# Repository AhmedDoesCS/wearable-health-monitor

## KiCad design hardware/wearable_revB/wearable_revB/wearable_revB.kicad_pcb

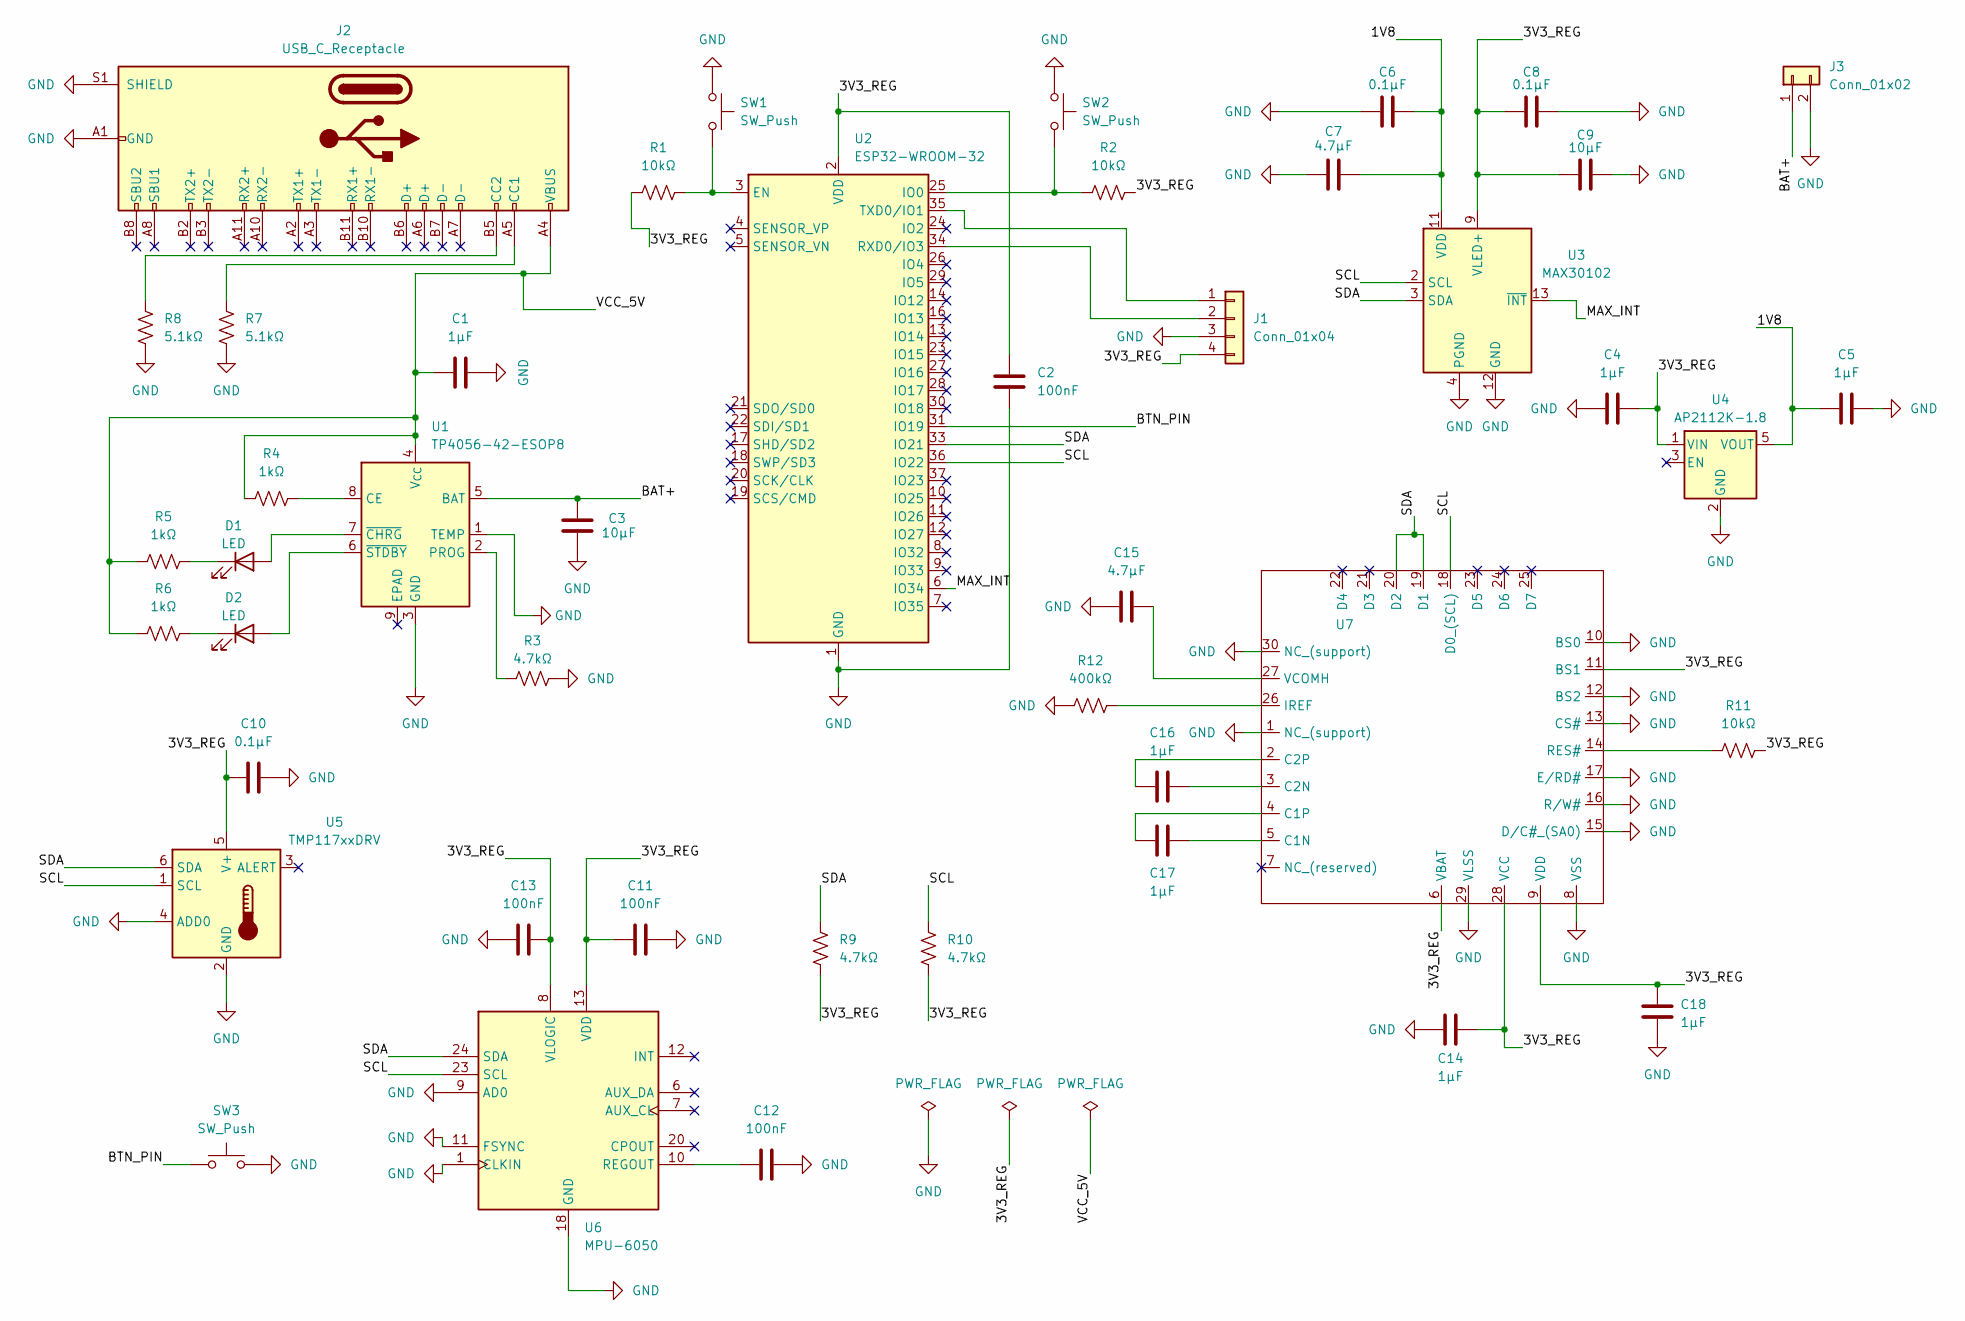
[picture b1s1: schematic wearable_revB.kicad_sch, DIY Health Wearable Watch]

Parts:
C1, C4, C5, C14, C16, C17, C18: 1µF; C_0603_1608Metric
C2, C11, C12, C13: 100nF; C_0603_1608Metric
C3, C9: 10µF; C_0603_1608Metric
C6, C8, C10: 0.1µF; C_0603_1608Metric
C7, C15: 4.7µF; C_0603_1608Metric
D1, D2: LED; LED_0603_1608Metric
J1: Conn_01x04; PinHeader_1x04_P1.27mm_Vertical_SMD_Pin1Left
J2: USB_C_Receptacle; USB_C_Receptacle_HRO_TYPE-C-31-M-12
J3: Conn_01x02; Battery_2Pin_THT
R1, R2, R11: 10kΩ; R_0603_1608Metric
R3, R9, R10: 4.7kΩ; R_0603_1608Metric
R4, R5, R6: 1kΩ; R_0603_1608Metric
R7, R8: 5.1kΩ; R_0603_1608Metric
R12: 400kΩ; R_0603_1608Metric
SW1, SW2: SW_Push; SW_SPST_B3U-1000P
SW3: SW_Push; SW_SPST_B3S-1100
U1: TP4056-42-ESOP8; SOIC-8-1EP_3.9x4.9mm_P1.27mm_EP2.41x3.3mm_ThermalVias
U2: ESP32-WROOM-32
U3: MAX30102; Maxim_OLGA-14_3.3x5.6mm_P0.8mm
U4: AP2112K-1.8; SOT-23-5
U5: TMP117xxDRV; WSON-6-1EP_2x2mm_P0.65mm_EP1x1.6mm
U6: MPU-6050; InvenSense_QFN-24_4x4mm_P0.5mm
U7: EASTRISING_ER-CON50HT-1

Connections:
/1V8: C5.1, C6.2, C7.1, U3.11 (VDD), U4.5 (VOUT)
/3V3_REG: C2.1, C4.2, C8.1, C9.1, C10.2, C11.1, C13.2, C14.2, C18.2, J1.4, R1.1, R2.2, R9.2, R10.2, R11.2, U2.2 (VDD), U3.9 (VLED+), U3.10 (VLED+), U4.1 (VIN), U5.5 (V+), U6.8 (VLOGIC), U6.13 (VDD), U7.6 (VBAT), U7.9 (VDD), U7.11 (BS1), U7.28 (VCC)
/BAT+: C3.1, J3.1, U1.5 (BAT)
/BTN_PIN: SW3.1, U2.31 (IO19)
/MAX_INT: U2.6 (IO34), U3.13 (~INT)
/SCL: R10.1, U2.36 (IO22), U3.2 (SCL), U5.1 (SCL), U6.23 (SCL), U7.18 (D0_(SCL))
/SDA: R9.1, U2.33 (IO21), U3.3 (SDA), U5.6 (SDA), U6.24 (SDA), U7.19 (D1), U7.20 (D2)
/VCC_5V: C1.1, J2.A4 (VBUS), J2.A9 (VBUS), J2.B4 (VBUS), J2.B9 (VBUS), R4.1, R5.1, R6.1, U1.4 (V_{CC})
GND: C1.2, C2.2, C3.2, C4.1, C5.2, C6.1, C7.2, C8.2, C9.2, C10.1, C11.2, C12.2, C13.1, C14.1, C15.1, C18.1, J1.3, J2.A1 (GND), J2.A12 (GND), J2.B1 (GND), J2.B12 (GND), J2.S1 (SHIELD), J3.2, R3.2, R7.2, R8.2, R12.1, SW1.1, SW2.1, SW3.2, U1.1 (TEMP), U1.3 (GND), U2.1 (GND), U2.15 (GND), U2.38 (GND), U2.39 (GND), U3.4 (PGND), U3.12 (GND), U4.2 (GND), U5.2 (GND), U5.4 (ADD0), U6.1 (CLKIN), U6.9 (AD0), U6.11 (FSYNC), U6.18 (GND), U7.1 (NC_(support)), U7.8 (VSS), U7.10 (BS0), U7.12 (BS2), U7.13 (CS#), U7.15 (D/C#_(SA0)), U7.16 (R/W#), U7.17 (E/RD#), U7.29 (VLSS), U7.30 (NC_(support))
unnamed: D1.2 (A), U1.7 (~CHRG)
unnamed: D1.1 (K), R5.2
unnamed: D2.2 (A), U1.6 (~STDBY)
unnamed: D2.1 (K), R6.2
unnamed: J1.1, U2.35 (TXD0/IO1)
unnamed: J1.2, U2.34 (RXD0/IO3)
unnamed: J2.A5 (CC1), R7.1
unnamed: J2.B5 (CC2), R8.1
unnamed: R4.2, U1.8 (CE)
unnamed: R3.1, U1.2 (PROG)
unnamed: R1.2, SW1.2, U2.3 (EN)
unnamed: R2.1, SW2.2, U2.25 (IO0)
unnamed: C12.1, U6.10 (REGOUT)
unnamed: C17.1, U7.5 (C1N)
unnamed: C17.2, U7.4 (C1P)
unnamed: C16.2, U7.3 (C2N)
unnamed: C16.1, U7.2 (C2P)
unnamed: R12.2, U7.26 (IREF)
unnamed: R11.1, U7.14 (RES#)
unnamed: C15.2, U7.27 (VCOMH)

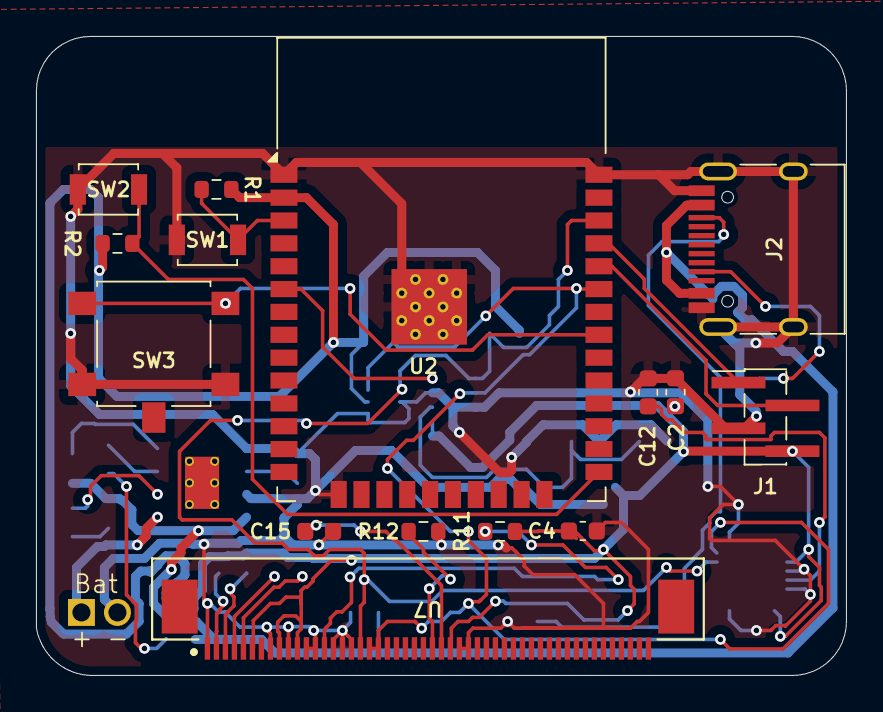
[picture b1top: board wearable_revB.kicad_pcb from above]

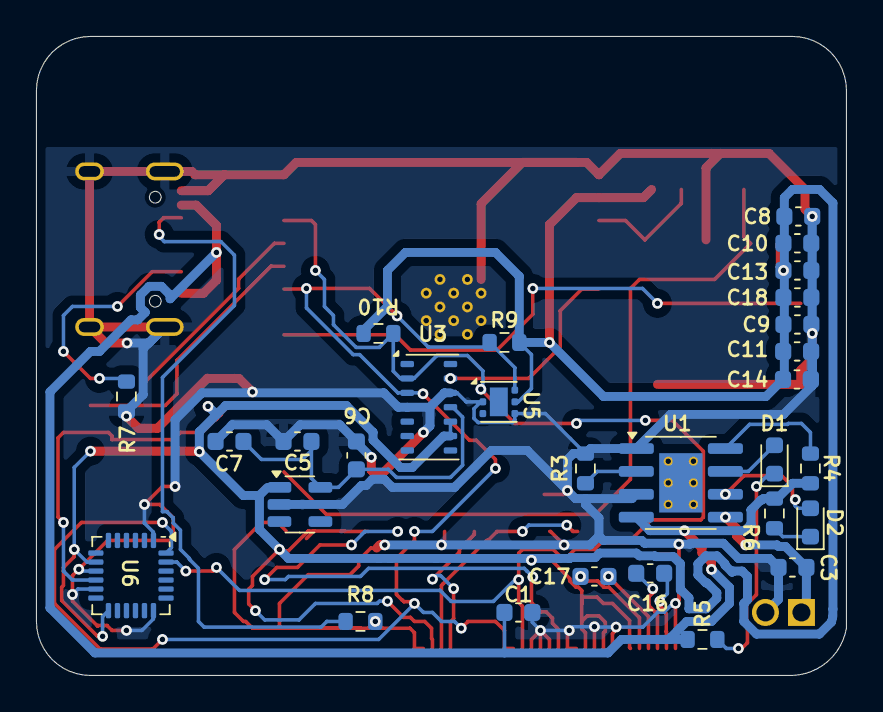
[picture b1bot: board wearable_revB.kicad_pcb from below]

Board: 2 copper layers, 45.0 x 35.5 mm, 45 parts (29 on the bottom side), 29 nets.

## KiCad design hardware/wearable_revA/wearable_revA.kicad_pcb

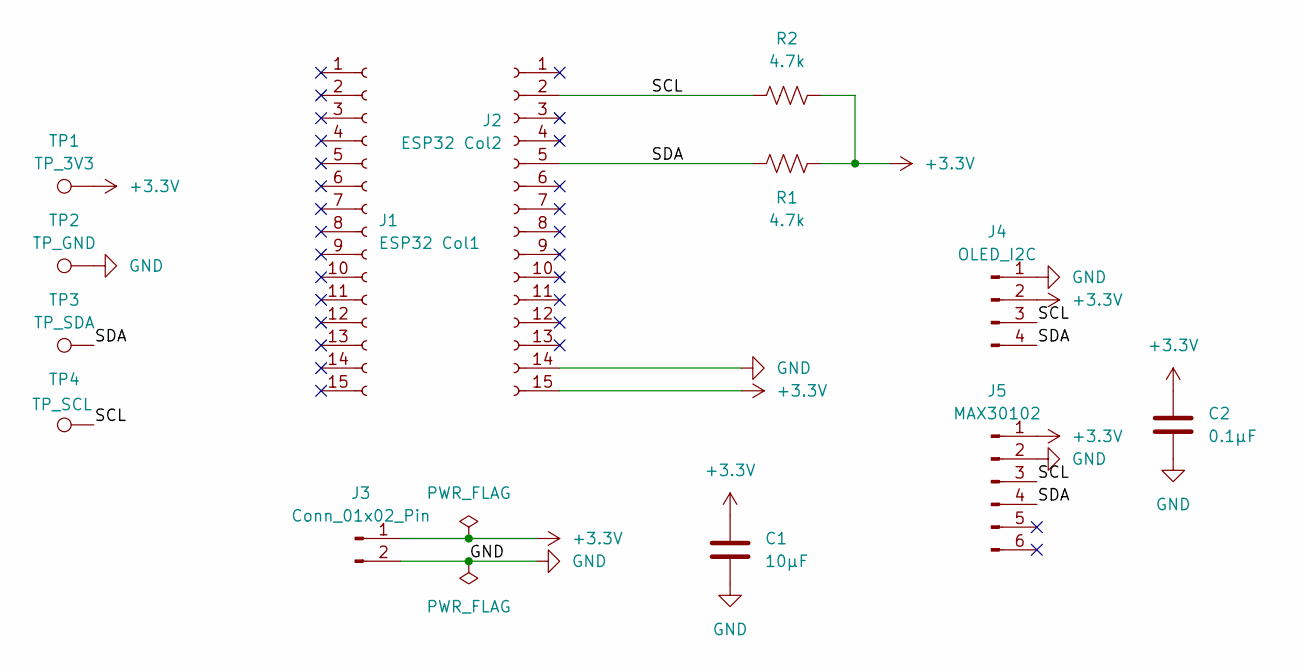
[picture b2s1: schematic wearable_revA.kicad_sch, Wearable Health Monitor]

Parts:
C1: 10µF; C_0603_1608Metric
C2: 0.1µF; C_0603_1608Metric
J1: ESP32 Col1; PinSocket_1x15_P2.54mm_Vertical
J2: ESP32 Col2; PinSocket_1x15_P2.54mm_Vertical
J3: Conn_01x02_Pin; PinHeader_1x02_P2.54mm_Vertical
J4: OLED_I2C; PinHeader_1x04_P2.54mm_Vertical
J5: MAX30102; PinHeader_1x06_P2.54mm_Vertical
R1, R2: 4.7k; R_0603_1608Metric
TP1: TP_3V3; TestPoint_Loop_D2.50mm_Drill1.0mm
TP2: TP_GND; TestPoint_Loop_D2.50mm_Drill1.0mm
TP3: TP_SDA; TestPoint_Pad_D1.5mm
TP4: TP_SCL; TestPoint_Pad_D1.5mm

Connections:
+3.3V: C1.1, C2.1, J2.15, J3.1, J4.2, J5.1, R1.2, R2.2, TP1.1
/SCL: J2.2, J4.3, J5.3, R2.1, TP4.1
/SDA: J2.5, J4.4, J5.4, R1.1, TP3.1
GND: C1.2, C2.2, J2.14, J3.2, J4.1, J5.2, TP2.1

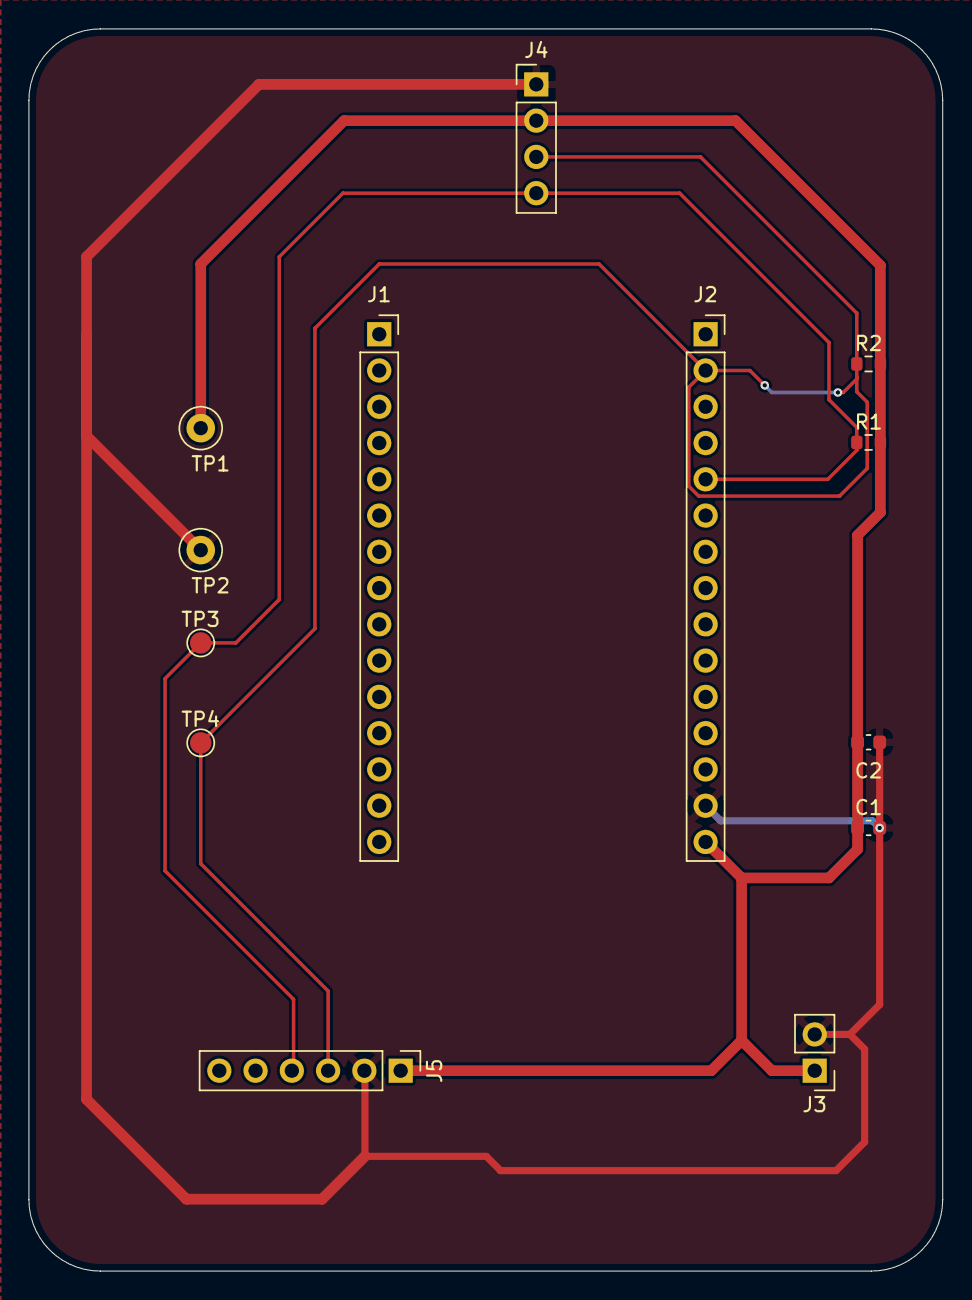
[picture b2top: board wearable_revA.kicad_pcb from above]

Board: 2 copper layers, 64.0 x 87.0 mm, 13 parts (0 on the bottom side), 4 nets.

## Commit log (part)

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2026-01-12 Set up project directories and log Update gitignore
2026-01-13 Initialize platformio subdirectory
2026-01-13 Initialize datasheet notes for sensors
2026-01-14 Initialize Rev A hardware project Remove platformio project
2026-01-14 Update Rev A schematic Include screenshot for proof
2026-01-16 Finalize Rev A PCB design Update log.md
2026-01-19 Fix log.md
2026-01-22 Initialize new firmware
2026-01-22 Transfer test program to main.cpp
2026-01-22 Include images in documentation
2026-01-22 Initialize MAX30102_test.cpp
2026-01-22 Include relevant libraries
2026-01-23 Include visual documentation for 2026-01-22 and update log.md
2026-01-23 Initialize software project
2026-01-24 Implement test code for data display
2026-02-08 Set up client ui tools
2026-02-08 Intialize server and database
2026-02-14 Start table design for UI
2026-02-14 Finalize activity route for database
2026-02-20 Develop MAX30102 and TMP117 schematics
